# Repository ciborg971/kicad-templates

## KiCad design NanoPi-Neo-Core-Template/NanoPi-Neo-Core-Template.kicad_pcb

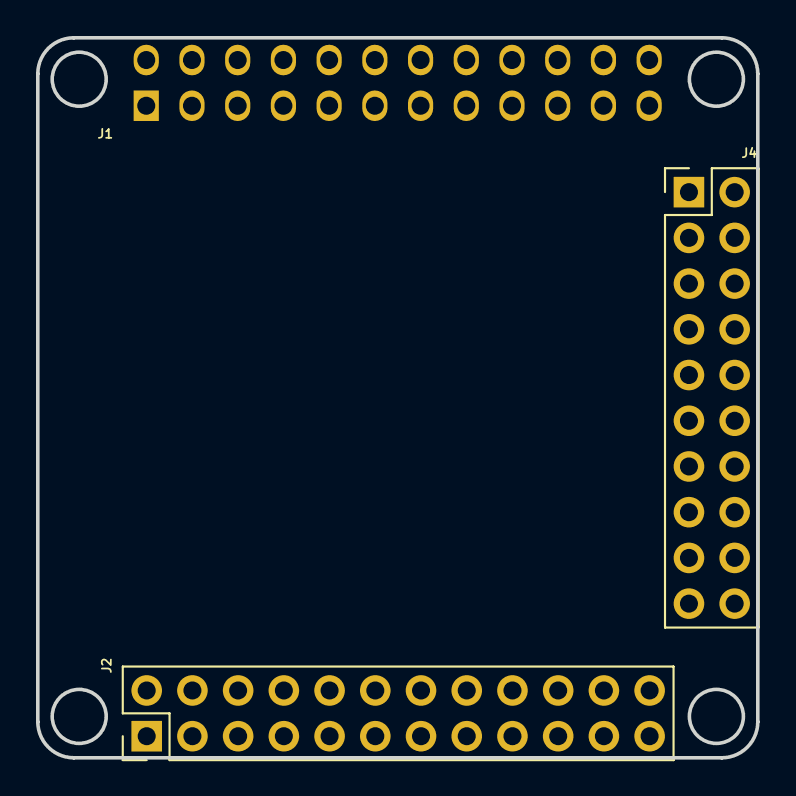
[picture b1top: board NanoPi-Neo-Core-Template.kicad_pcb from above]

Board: 2 copper layers, 40.0 x 40.0 mm, 7 parts (1 on the bottom side), 4 nets, no tracks yet.

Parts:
H1, H2, H3, H4: MountingHole; MountingHole_3mm
J1: GPIO; Socket_Strip_Straight_2x12_Pitch2.54mm
J2: GPIO; PinHeader_2x12_P2.54mm_Vertical
J4: Conn_02x10_Odd_Even; PinHeader_2x10_P2.54mm_Vertical

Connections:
+3V3: J1.1, J1.17, J4.20
+5V: J1.2, J1.4, J2.1, J2.22, J4.17, J4.19
/NC: J4.7, J4.8, J4.9, J4.10
GND: J1.6, J1.9, J1.14, J1.20, J2.23, J2.24, J4.11, J4.12

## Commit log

2023-03-14 Add NanoPi Neo Core template
